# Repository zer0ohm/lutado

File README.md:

# Lutado
Hotplate reflow soldering controller

## What's meaning Lutado
* Lutado is an Esperanto word meaning "Soldering".

## What in this repository
* 

## License
* Hardware Design files: [CC-BY-SA 4.0](https://creativecommons.org/licenses/by-sa/4.0/)
* Firmware files: [GNU LGPL](https://www.gnu.org/licenses/#LGPL)

## Disclaimer
There is no warranty, expressed or implied, associated with files in this project. Especially there is a AC high voltage(and large current!) shock hazard which can kill you. Use at your own risk.

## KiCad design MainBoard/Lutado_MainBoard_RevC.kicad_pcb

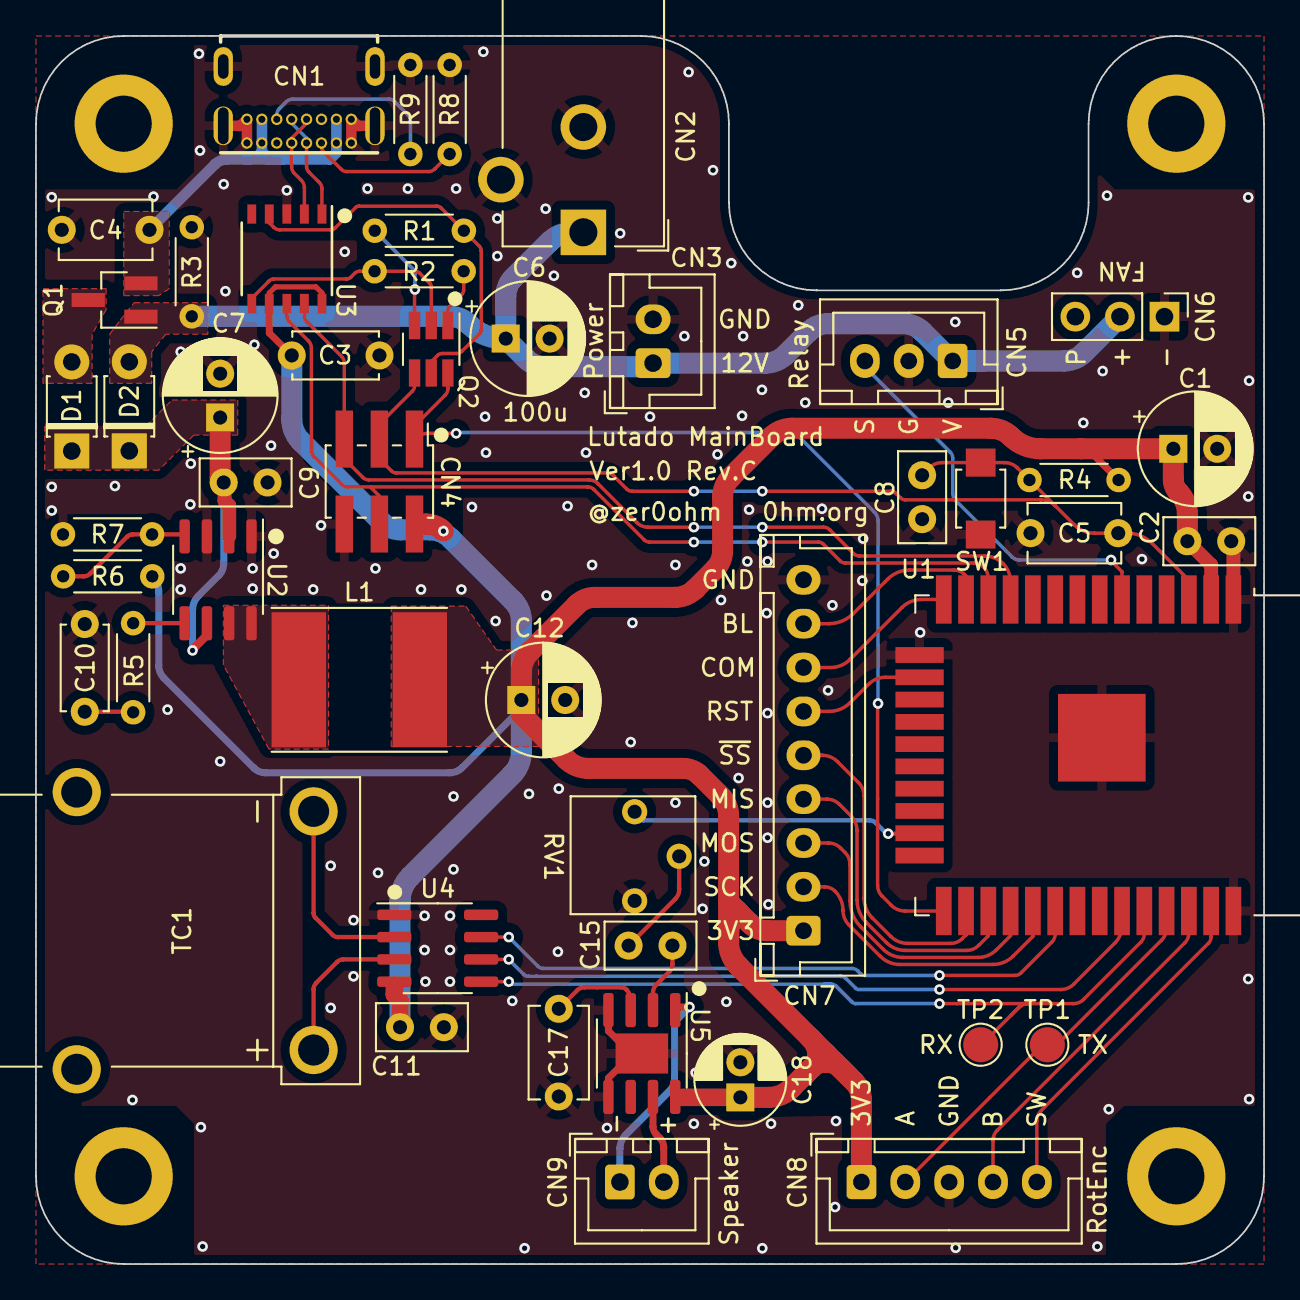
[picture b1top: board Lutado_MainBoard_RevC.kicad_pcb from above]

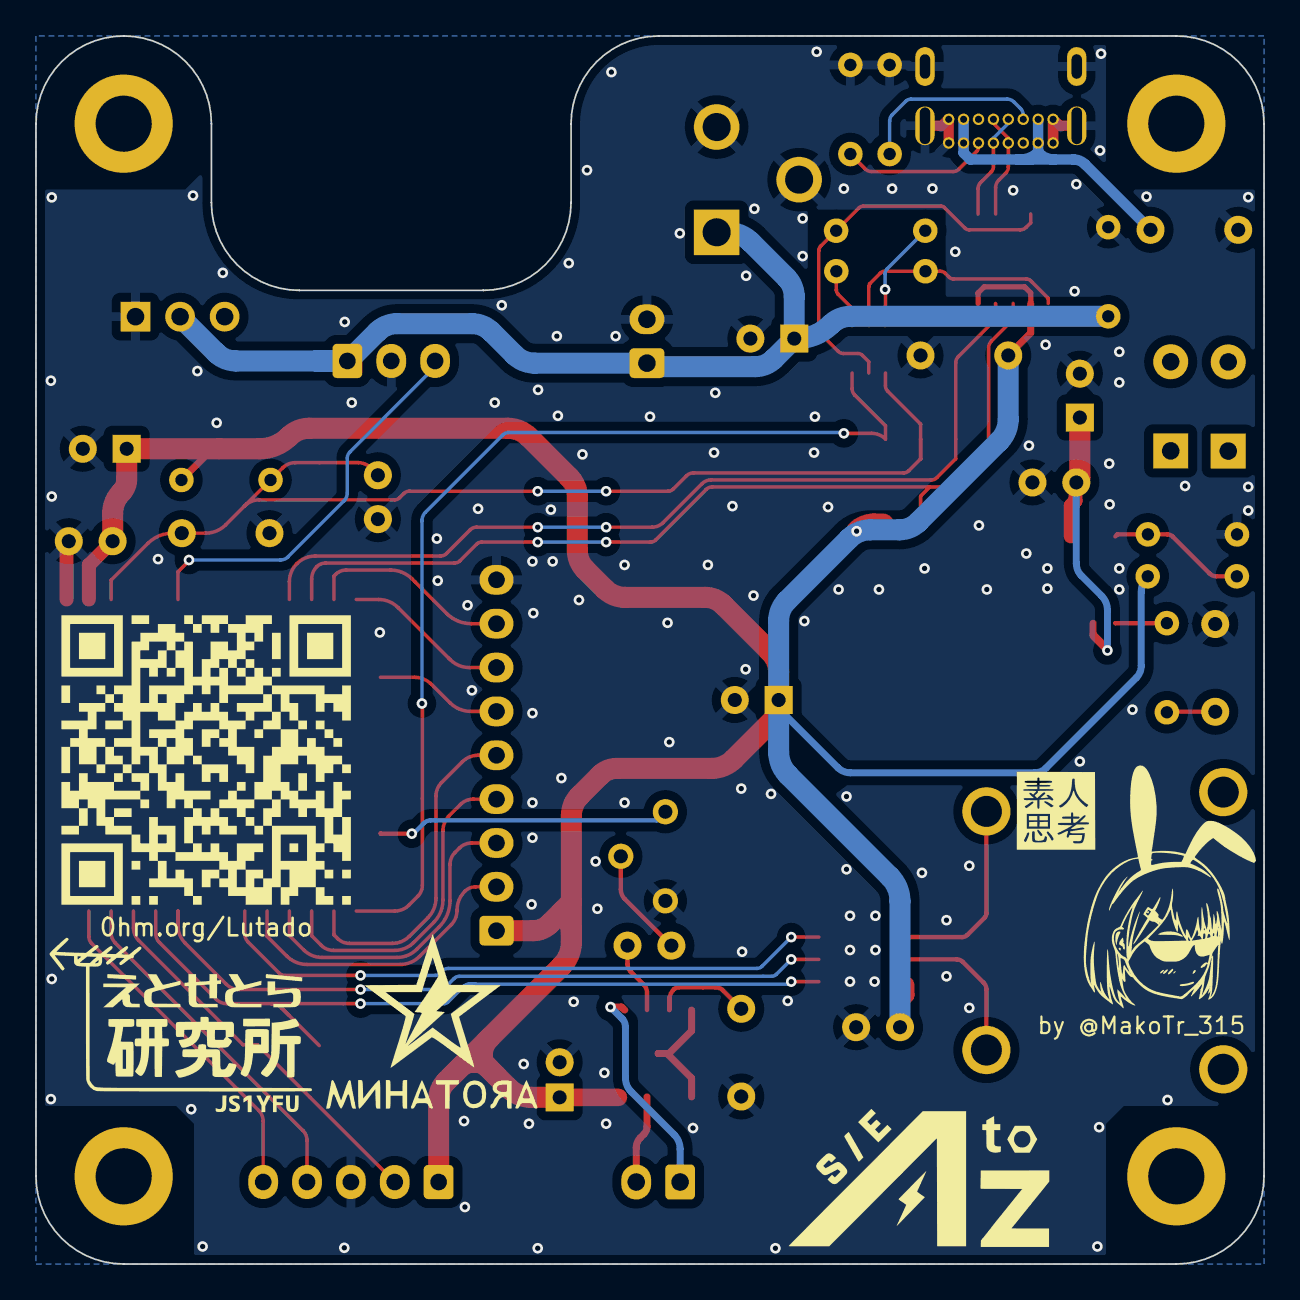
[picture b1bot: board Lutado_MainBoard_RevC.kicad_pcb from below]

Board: 2 copper layers, 70.0 x 70.0 mm, 57 parts (5 on the bottom side), 44 nets.

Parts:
C1, C12: 56u; CP_Radial_D6.3mm_P2.50mm
C2, C8, C9, C11, C15: 0.1u; C_Disc_D5.0mm_W2.5mm_P2.50mm
C3: 0.33u; C_Disc_D4.7mm_W2.5mm_P5.00mm
C4: 2.2u; C_Disc_D5.1mm_W3.2mm_P5.00mm
C5, C17: 1u; C_Disc_D5.1mm_W3.2mm_P5.00mm
C6: 100u; CP_Radial_D6.3mm_P2.50mm
C7: 22u; CP_Radial_D6.3mm_P2.50mm
C10: 6.8n; C_Disc_D4.7mm_W2.5mm_P5.00mm
C18: 100u; CP_Radial_D5.0mm_P2.00mm
CN1: USB4085-GF-A; GCT_USB4085-GF-A_REVA
CN2: PJ-102A; BarrelJack_CUI_PJ-102AH_Horizontal
CN3, CN9: B2B-XH-A; JST_XH_B2B-XH-A_1x02_P2.50mm_Vertical
CN4: Conn_02x03; PinHeader_2x03_P2.00mm_Vertical_SMD
CN5: B3B-XH-A; JST_XH_B3B-XH-A_1x03_P2.50mm_Vertical
CN6: Conn_01x03; PinHeader_1x03_P2.54mm_Vertical
CN7: B9B-XH-A; JST_XH_B9B-XH-A_1x09_P2.50mm_Vertical
CN8: B5B-XH-A; JST_XH_B5B-XH-A_1x05_P2.50mm_Vertical
D1, D2: 1S4; D_T-1_P5.08mm_Horizontal
G1: LOGO; Minatoya
G2: LOGO; et_cetera_lab
G3: LOGO; AtoZ2022
G4: LOGO; amateur_intent_invert
L1: 4.7uH; L_Taiyo-Yuden_NR-80xx_HandSoldering
MH1, MH2, MH3, MH4: MountingHole_3.2mm_M3_DIN965_Pad
Q1: IRLML6402; SOT-23_Handsoldering
Q2: FMBA06; SOT-23-6_Handsoldering
QR*****: Lutado_PJ-URL_QR
R1, R2, R3, R4: 10k; R_Axial_DIN0204_L3.6mm_D1.6mm_P5.08mm_Horizontal
R5: 16k; R_Axial_DIN0204_L3.6mm_D1.6mm_P5.08mm_Horizontal
R6: 7.5k; R_Axial_DIN0204_L3.6mm_D1.6mm_P5.08mm_Horizontal
R7: 2.4k; R_Axial_DIN0204_L3.6mm_D1.6mm_P5.08mm_Horizontal
R8, R9: 5.1k; R_Axial_DIN0204_L3.6mm_D1.6mm_P5.08mm_Horizontal
RV1: 10k; Potentiometer_Bourns_3362P_Vertical
SW1: B3U-1000P; SW_SPST_B3U-1000P
TC1: PCC-SMP-K; Omega_PCC-SMP-K
TP1: ORG_TX; TestPoint_Pad_D2.0mm
TP2: ORG_RX; TestPoint_Pad_D2.0mm
U1: ESP32-WROOM-32E; ESP32-WROOM-32x_KeepoutZone_Fixed
U2: BD9C301FJ; SOIC-8_3.9x4.9mm_P1.27mm
U3: CH340K; SSOP-10_3.9x4.9mm_P1.00mm
U4: MAX31855KASA; SOIC-8_3.9x4.9mm_P1.27mm
U5: HT82V739/A; SOIC-8-1EP_3.9x4.9mm_P1.27mm_EP2.29x3mm

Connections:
+3V3: C1.1, C2.1, C3.1, C11.2, C12.1, C18.1, CN4.2, CN7.1, CN8.1, L1.2, R4.1, R6.1, U1.2 (3V3), U3.7 (VCC), U3.10 (V3), U4.4 (VCC), U5.8 (VDD)
+12V: C6.1, CN2.1, CN3.1, CN5.1, CN6.2, D2.2 (A), Q1.1 (G), R3.2
/BOOT0: CN4.1, Q2.6 (C1), U1.25 (IO0)
/COMP: R5.1, U2.5 (COMP)
/DAT_COM: CN7.7, U1.14 (IO12)
/DP_BL: CN7.8, U1.13 (IO14)
/DP_RST: CN7.6, U1.16 (IO13)
/EN: C5.1, C8.2, CN4.3, Q2.4 (C2), R4.2, SW1.1, U1.3 (EN)
/FB: R6.2, R7.1, U2.4 (FB)
/RS_A: CN8.2, TP1.1, U1.35 (IO1)
/RS_B: CN8.4, U1.36 (IO22)
/RS_S: CN8.5, U1.37 (IO23)
/SSPI_MISO: U1.30 (IO18), U4.7 (SO)
/SSPI_SCK: TP2.1, U1.34 (IO3), U4.5 (SCK)
/SSPI_~SS: U1.33 (IO21), U4.6 (~CS)
/SW: L1.1, U2.7 (SW), U2.8 (SW)
/SWR: CN5.3, U1.6 (IO34)
/S_AUD: RV1.1, U1.23 (IO15)
/S_OUTN: CN9.1, U5.1 (OUTN)
/S_OUTP: CN9.2, U5.7 (OUTP)
/USART_RX: CN4.4, U1.12 (IO27), U3.8 (TXD)
/USART_TX: CN4.5, U1.11 (IO26), U3.9 (RXD)
/USBD+: CN1.A6 (D+), CN1.B6 (D+), U3.1 (UD+)
/USBD-: CN1.A7 (D-), CN1.B7 (D-), U3.2 (UD-)
/VSEL: C7.1, C9.1, D1.1 (K), D2.1 (K), U2.2 (VIN), U2.6 (EN)
/VSPI_MISO: CN7.4, U1.27 (IO16)
/VSPI_MOSI: CN7.3, U1.28 (IO17)
/VSPI_SCK: CN7.2, U1.29 (IO5)
/VSPI_~SS: CN7.5, U1.26 (IO4)
/~DTR: Q2.5 (E1), R1.1, U3.4 (~DTR)
/~RTS: Q2.2 (E2), R2.1, U3.6 (~RTS)
GND: C1.2, C2.2, C3.2, C4.1, C5.2, C6.2, C7.2, C8.1, C9.2, C10.2, C11.1, C12.2, C17.2, C18.2, CN1.A1 (GND), CN1.A12 (GND), CN1.B1 (GND), CN1.B12 (GND), CN1.S1 (SHIELD), CN2.2, CN2.3, CN3.2, CN4.6, CN5.2, CN6.1, CN7.9, CN8.3, R3.1, R7.2, R8.2, R9.2, RV1.3, SW1.2, U1.1 (GND), U1.15 (GND), U1.38 (GND), U1.39 (EPAD), U2.1 (PGND), U2.3 (AGND), U3.3 (GND), U4.1 (GND), U5.4 (VSS), U5.5 (~CE), U5.9 (E-PAD)
unnamed: C10.1, R5.2
unnamed: C15.1, U5.2 (AUD_IN)
unnamed: C15.2, RV1.2
unnamed: C17.1, U5.3 (VREF)
unnamed: CN1.A5 (CC1), R8.1
unnamed: CN1.B5 (CC2), R9.1
unnamed: D1.2 (A), Q1.3 (D)
unnamed: Q2.1 (B1), R2.2
unnamed: Q2.3 (B2), R1.2
unnamed: TC1.1 (+), U4.3 (T+)
unnamed: TC1.2 (-), U4.2 (T-)
VBUS: C4.2, CN1.A4 (VBUS), CN1.A9 (VBUS), CN1.B4 (VBUS), CN1.B9 (VBUS), Q1.2 (S)

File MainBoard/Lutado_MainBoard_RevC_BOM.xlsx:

Item | Category | Reference(s) | Qty | Value | Recommend | Alternate source | MPN | Notes
1 | コンデンサ | C1, C12 | 2 | 56uF | 秋月電子(P-08295) |  | 25SEPF56M
2 | コンデンサ | C2, C8, C9, C11, C15 | 5 | 0.1uF | 秋月電子(P-13582) |  | RDER71H104K0P1H03B
3 | コンデンサ | C3 | 1 | 0.33uF | 秋月電子(P-08147) |  | RDER71H334K1K1H03B
4 | コンデンサ | C4 | 1 | 2.2uF | 秋月電子(P-08152) |  | RDER71H225K2K1H03B
5 | コンデンサ | C5, C17 | 2 | 1uF | 秋月電子(P-08150) |  | RDER71H105K2K1H03B
6 | コンデンサ | C6 | 1 | 100uF(OS-CON) | 秋月電子(P-08290) |  | 16SEPC100M | DCジャック側バイパスコンデンサガワ
7 | コンデンサ | C7 | 1 | 22uF | 秋月電子(P-08294) |  | 35SEPF22M
8 | コンデンサ | C10 | 1 | 6.8nF(6800pF) | 秋月電子(P-08137) |  | RDER71H682K0K1H03B
9 | コンデンサ | C18 | 1 | 100uF(PK) | 秋月電子(P-03122) |  | 25PK100MEFC5X11 | スピーカーアンプIC用バイパスコンデンサヨウ
10 | コネクタ | CN1 | 1 | USB4085-GF-A | マルツ |  | USB4085-GF-A
11 | コネクタ | CN2 | 1 | PJ-102A/18742 | 秋月電子(C-09408) |  | PJ-102A/18742
12 | コネクタ | CN3, CN9 | 2 | B2B-XH-A | 秋月電子(C-12247) | 秋月電子(C-17150) | B2B-XH-A(LF)(SN) | XHP-2とセット
13 | コネクタ | CN4 | 1 | Conn_02x03 | マルツ |  | TMM-103-01-T-D-SM-P-TR
14 | コネクタ | CN5 | 1 | B3B-XH-A | 秋月電子(C-12248) | 秋月電子(C-17151) | B3B-XH-A(LF)(SN) | XHP-3とセット
15 | コネクタ | CN6 | 1 | Conn_01x03 | 秋月電子(C-03949) |  | PH-1X3SG
16 | コネクタ | CN7 | 1 | B9B-XH-A | 秋月電子(C-13890) |  | B9B-XH-A(LF)(SN) | XHP-9とセット
17 | コネクタ | CN8, XCN1 | 2 | B5B-XH-A | 秋月電子(C-12250) | 秋月電子(C-17153) | B5B-XH-A(LF)(SN) | XHP-5とセット
18 | ダイオード | D1, D2 | 2 | 1S4 | 秋月電子(I-00127)アキツキデンシ |  | 1S4
19 | インダクタ | L1 | 1 | 4.7uH | マルツ |  | NRS8040T4R7NJGJ
20 | LCDモジュール | M1 | 1 | DFR0669 |  |  | DFR0669 | オプション
21 | MOSFET | Q1 | 1 | IRLML6402 | 秋月電子(I-02553) |  | IRLML6402TRPBF
22 | トランジスタ | Q2 | 1 | FMBA06 | マルツ | マルツ(FMB2222A) | FMBA06/FMB2222A | 同一パッケージ/ピン配置品ドウイツハイチヒン
23 | 抵抗テイコウ | R1, R2, R3, R4 | 4 | 10kΩ | マルツ |  | MFS1/4CC1002F
24 | 抵抗テイコウ | R5 | 1 | 16kΩ | マルツ |  | MFS1/4CC1602F
25 | 抵抗テイコウ | R6 | 1 | 7.5kΩ | マルツ |  | MFS1/4CC7501F
26 | 抵抗テイコウ | R7 | 1 | 2.4kΩ | マルツ |  | MFS1/4CC2401F
27 | 抵抗テイコウ | R8, R9 | 2 | 5.1kΩ | マルツ |  | MFS1/4CC5101F
28 | 可変抵抗カヘンテイコウ | RV1 | 1 | 10kΩ | 秋月電子(P-03277) |  | 3362P-1-103LF
29 | スイッチ | SW1 | 1 | B3U-1000P | マルツ |  | B3U-1000P
30 | コネクタ(特殊)トクシュ | TC1 | 1 | PCC-SMP-K | 秋月電子(P-14972) |  | PCC-SMP-K-ROHS
31 | IC | U1 | 1 | ESP32-WROOM-32E | 秋月電子(M-15675) |  | ESP32-WROOM-32E(16MB)
32 | IC | U2 | 1 | BD9C301FJ | マルツ |  | BD9C301FJ-E2
33 | IC | U3 | 1 | CH340K | 秋月電子(I-16306) |  | CH340K
34 | IC | U4 | 1 | MAX31855KASA | 秋月電子(I-14486) |  | MAX31855KASA
35 | IC | U5 | 1 | HT82V739A |  |  | HT82V739A | オプション
36 |  | XC1, XC2 | 2 | 10nF(0.01uF) | 秋月電子(P-13699) |  | GRM21BC72A105KE01
37 |  | XR1, XR2, XR3 | 3 | 10kΩ | マルツ |  | RK73B2ATTD103J
38 |  | XSW1 | 1 | EC12PLRGBSDVBF | 秋月電子(P-05773) |  | EC12PLRGBSDVBF-D-25K-24-24C-61

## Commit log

2022-08-07 Update README.md
    add license and disclaimer
2022-08-07 add PCB designs
2022-08-07 add kicad symbols
